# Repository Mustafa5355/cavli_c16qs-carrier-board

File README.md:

# cavli_c16qs-carrier-board

This repository contains the complete hardware design for a 2-layer carrier board for the Cavli C16QS LTE Cat-1 bis module. The board provides regulated power, SIM card interface, RF antenna connection via u.FL, level-shifted UART communication to a 3.3 V host, and control/status signals.

The design is implemented in KiCad and follows Cavli's hardware guidelines for power integrity, RF layout, and SIM protection. It is intended as a reference carrier for evaluation, prototyping, and integration of the C16QS module into embedded systems.

Features:
- 5 V input with synchronous buck regulation to module VBAT
- Nano-SIM socket with ESD protection and signal conditioning
- u.FL connector for external LTE antenna
- Bidirectional UART level shifting between 1.8 V and 3.3 V domains
- Hardware power key, reset, and network status indication
- 2-layer, low-cost PCB optimized for EMI and signal integrity

The repository includes schematic, PCB layout, fabrication outputs, BOM, and design documentation.

## Footprint Note

The C16QS footprint included in this repository was created manually by the author using the published mechanical drawings and pin mapping of the C16QS module. It is designed to be reusable across projects and is suitable for prototyping and evaluation.

This footprint is not an official manufacturer CAD file. Users should verify alignment and pin mapping against the latest Cavli documentation before fabrication.

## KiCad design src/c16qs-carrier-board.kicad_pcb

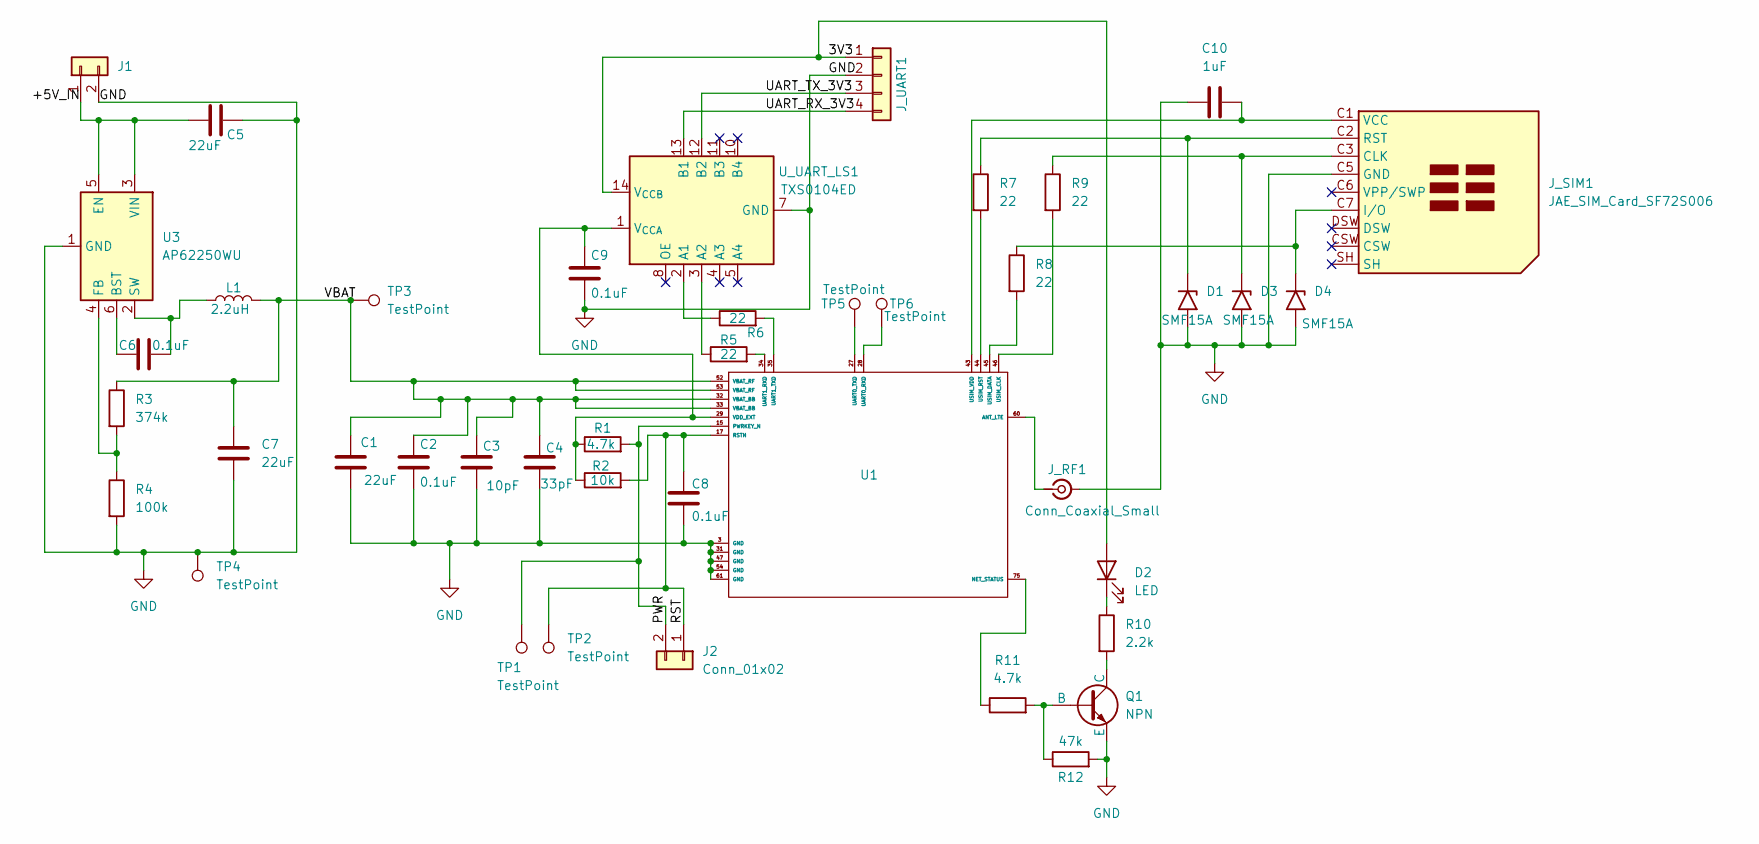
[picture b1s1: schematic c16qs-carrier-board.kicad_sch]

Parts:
C1, C5, C7: 22uF; C_0805_2012Metric
C2, C6, C8, C9: 0.1uF; C_0402_1005Metric
C3: 10pF; C_0402_1005Metric
C4: 33pF; C_0402_1005Metric
C10: 1uF; C_0603_1608Metric
D1, D3, D4: SMF15A; D_SOD-123
D2: LED; LED_0201_0603Metric
J1, J2: Conn_01x02; PinHeader_1x02_P2.54mm_Vertical
J_RF1: Conn_Coaxial_Small; U.FL_Hirose_U.FL-R-SMT-1_Vertical
J_SIM1: JAE_SIM_Card_SF72S006
J_UART1: Conn_01x04; PinHeader_1x04_P2.54mm_Vertical
L1: 2.2uH; L_1210_3225Metric
Q1: NPN; SOT-23
R1, R11: 4.7k; R_0402_1005Metric
R2: 10k; R_0402_1005Metric
R3: 374k; R_0402_1005Metric
R4: 100k; R_0402_1005Metric
R5, R6, R7, R8, R9: 22; R_0402_1005Metric
R10: 2.2k; R_0402_1005Metric
R12: 47k; R_0402_1005Metric
TP1, TP2, TP3, TP4, TP5, TP6: TestPoint; TestPoint_Pad_D1.0mm
U1: C16QS
U3: AP62250WU; TSOT-23-6
U_UART_LS1: TXS0104ED; SOIC-14_3.9x8.7mm_P1.27mm

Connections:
/3V3: D2.2 (A), J_UART1.1, U_UART_LS1.14 (V_{CCB})
/+5V_IN: C5.2, J1.1, U3.3 (VIN), U3.5 (EN)
/PWR: J2.2, R1.2, TP1.1, U1.15 (PWRKEY_N)
/RST: C8.1, J2.1, R2.2, TP2.1, U1.17 (RSTN)
/UART_RX_3V3: J_UART1.4, U_UART_LS1.13 (B1)
/UART_TX_3V3: J_UART1.3, U_UART_LS1.12 (B2)
/VBAT: C1.1, C2.1, C3.1, C4.1, C7.1, L1.2, R3.1, TP3.1, U1.32 (VBAT_BB), U1.33 (VBAT_BB), U1.52 (VBAT_RF), U1.53 (VBAT_RF)
GND: C1.2, C2.2, C3.2, C4.2, C5.1, C7.2, C8.2, C9.2, C10.1, D1.2 (A2), D3.2 (A2), D4.2 (A2), J1.2, J_RF1.2 (Ext), J_SIM1.C5 (GND), J_UART1.2, Q1.3 (E), R4.2, R12.2, TP4.1, U1.3 (GND), U1.31 (GND), U1.47 (GND), U1.54 (GND), U1.61 (GND), U3.1 (GND), U_UART_LS1.7 (GND)
unnamed: D1.1 (A1), J_SIM1.C2 (RST), R7.1
unnamed: D2.1 (K), R10.1
unnamed: D3.1 (A1), J_SIM1.C3 (CLK), R9.1
unnamed: D4.1 (A1), J_SIM1.C7 (I/O), R8.1
unnamed: J_RF1.1 (In), U1.60 (ANT_LTE)
unnamed: C10.2, J_SIM1.C1 (VCC), U1.43 (USIM_VDD)
unnamed: Q1.2 (B), R11.2, R12.1
unnamed: Q1.1 (C), R10.2
unnamed: R11.1, U1.75 (NET_STATUS)
unnamed: TP6.1, U1.28 (UART0_RXD)
unnamed: TP5.1, U1.27 (UART0_TXD)
unnamed: R5.2, U1.34 (UART1_RXD)
unnamed: R6.2, U1.35 (UART1_TXD)
unnamed: R9.2, U1.46 (USIM_CLK)
unnamed: R8.2, U1.45 (USIM_DATA)
unnamed: R7.2, U1.44 (USIM_RST)
unnamed: C9.1, R1.1, R2.1, U1.29 (VDD_EXT), U_UART_LS1.1 (V_{CCA})
unnamed: C6.1, U3.6 (BST)
unnamed: R3.2, R4.1, U3.4 (FB)
unnamed: C6.2, L1.1, U3.2 (SW)
unnamed: R6.1, U_UART_LS1.2 (A1)
unnamed: R5.1, U_UART_LS1.3 (A2)

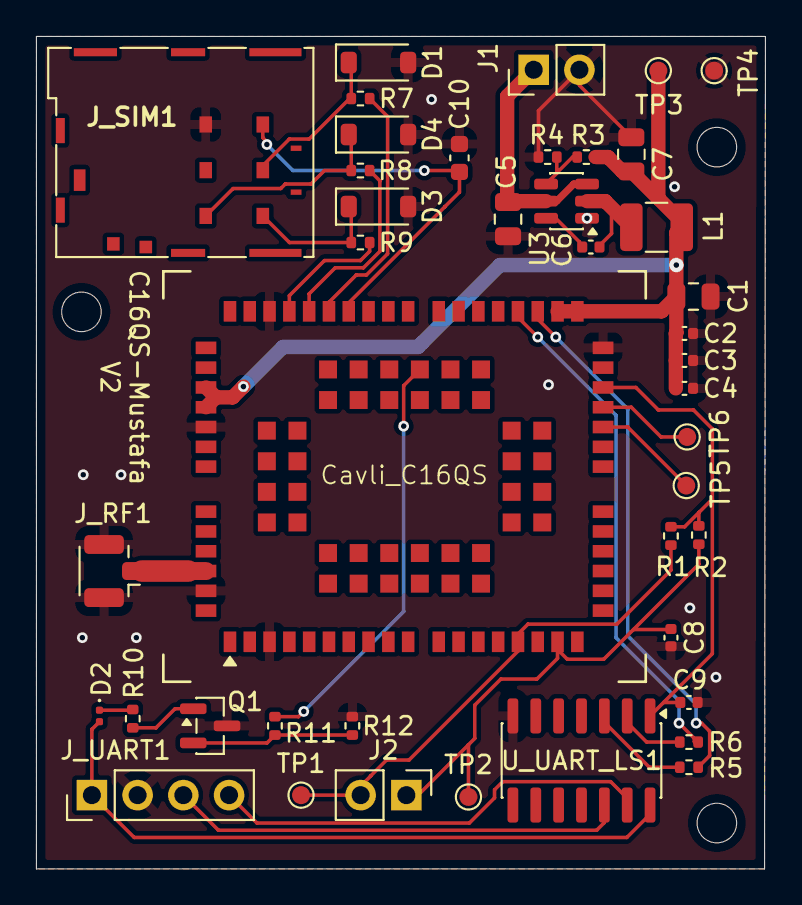
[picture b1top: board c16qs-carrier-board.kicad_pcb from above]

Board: 2 copper layers, 40.5 x 46.2 mm, 42 parts (0 on the bottom side), 30 nets.
